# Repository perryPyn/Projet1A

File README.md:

Ce projet, réalisé dans le cadre du Semestre 6 à l'ENSEA (Année 2025-2026), consiste à développer un prototype de mesure de distance basé sur la technologie Time Of Flight (TOF). L'objectif est d'utiliser un capteur laser compact pour détecter des obstacles et commander une interface visuelle de retour.

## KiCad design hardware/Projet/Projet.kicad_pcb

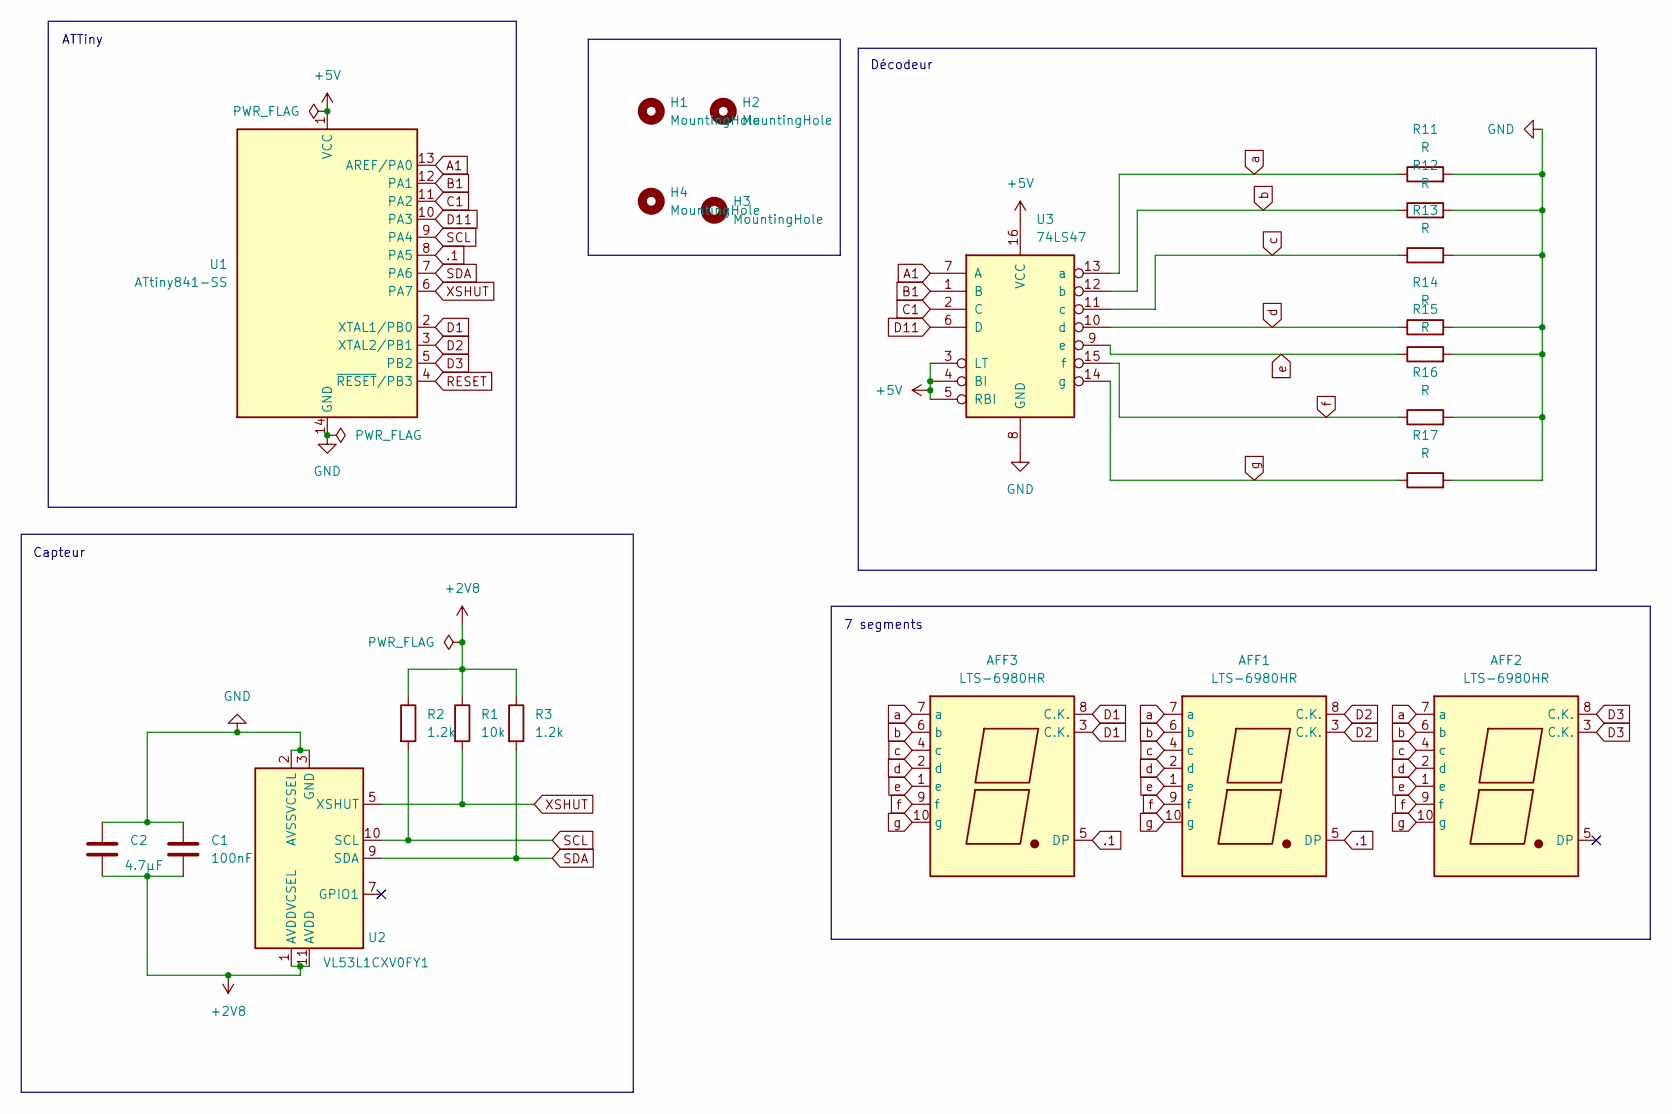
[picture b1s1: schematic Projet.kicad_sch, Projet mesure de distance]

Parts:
AFF1, AFF2, AFF3: LTS-6980HR; Sans titre_1
C1: 100nF; C_0603_1608Metric_Pad1.08x0.95mm_HandSolder
C2: 4.7µF; C_0603_1608Metric_Pad1.08x0.95mm_HandSolder
H1, H2, H3, H4: MountingHole; MountingHole_3.2mm_M3_DIN965_Pad
R1: 10k; R_0201_0603Metric_Pad0.64x0.40mm_HandSolder
R2, R3: 1.2k; R_0201_0603Metric_Pad0.64x0.40mm_HandSolder
R11, R12, R13, R14, R15, R16, R17: R; R_0201_0603Metric_Pad0.64x0.40mm_HandSolder
U1: ATtiny841-SS; SOIC-14_3.9x8.7mm_P1.27mm
U2: VL53L1CXV0FY1; ST_VL53L1x
U3: 74LS47; DIP-16_W7.62mm_SMDSocket_SmallPads

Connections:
+2V8: C1.2, C2.2, R1.1, R2.1, R3.1, U2.1 (AVDDVCSEL), U2.11 (AVDD)
+5V: U1.1 (VCC), U3.3 (LT), U3.4 (BI), U3.5 (RBI), U3.16 (VCC)
.1: AFF1.5 (DP), AFF3.5 (DP), U1.8 (PA5)
A1: U1.13 (AREF/PA0), U3.7 (A)
B1: U1.12 (PA1), U3.1 (B)
C1: U1.11 (PA2), U3.2 (C)
D1: AFF3.3 (C.K.), AFF3.8 (C.K.), U1.2 (XTAL1/PB0)
D2: AFF1.3 (C.K.), AFF1.8 (C.K.), U1.3 (XTAL2/PB1)
D3: AFF2.3 (C.K.), AFF2.8 (C.K.), U1.5 (PB2)
D11: U1.10 (PA3), U3.6 (D)
GND: C1.1, C2.1, R11.2, R12.2, R13.2, R14.2, R15.2, R16.2, R17.2, U1.14 (GND), U2.2 (AVSSVCSEL), U2.3 (GND), U2.4 (GND), U2.6 (GND), U2.12 (GND), U3.8 (GND)
RESET: U1.4 (~RESET/PB3)
SCL: R2.2, U1.9 (PA4), U2.10 (SCL)
SDA: R3.2, U1.7 (PA6), U2.9 (SDA)
XSHUT: R1.2, U1.6 (PA7), U2.5 (XSHUT)
a: AFF1.7 (a), AFF2.7 (a), AFF3.7 (a), R11.1, U3.13 (a)
b: AFF1.6 (b), AFF2.6 (b), AFF3.6 (b), R12.1, U3.12 (b)
c: AFF1.4 (c), AFF2.4 (c), AFF3.4 (c), R13.1, U3.11 (c)
d: AFF1.2 (d), AFF2.2 (d), AFF3.2 (d), R14.1, U3.10 (d)
e: AFF1.1 (e), AFF2.1 (e), AFF3.1 (e), R15.1, U3.9 (e)
f: AFF1.9 (f), AFF2.9 (f), AFF3.9 (f), R16.1, U3.15 (f)
g: AFF1.10 (g), AFF2.10 (g), AFF3.10 (g), R17.1, U3.14 (g)

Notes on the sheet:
Capteur
ATTiny
7 segments
Décodeur

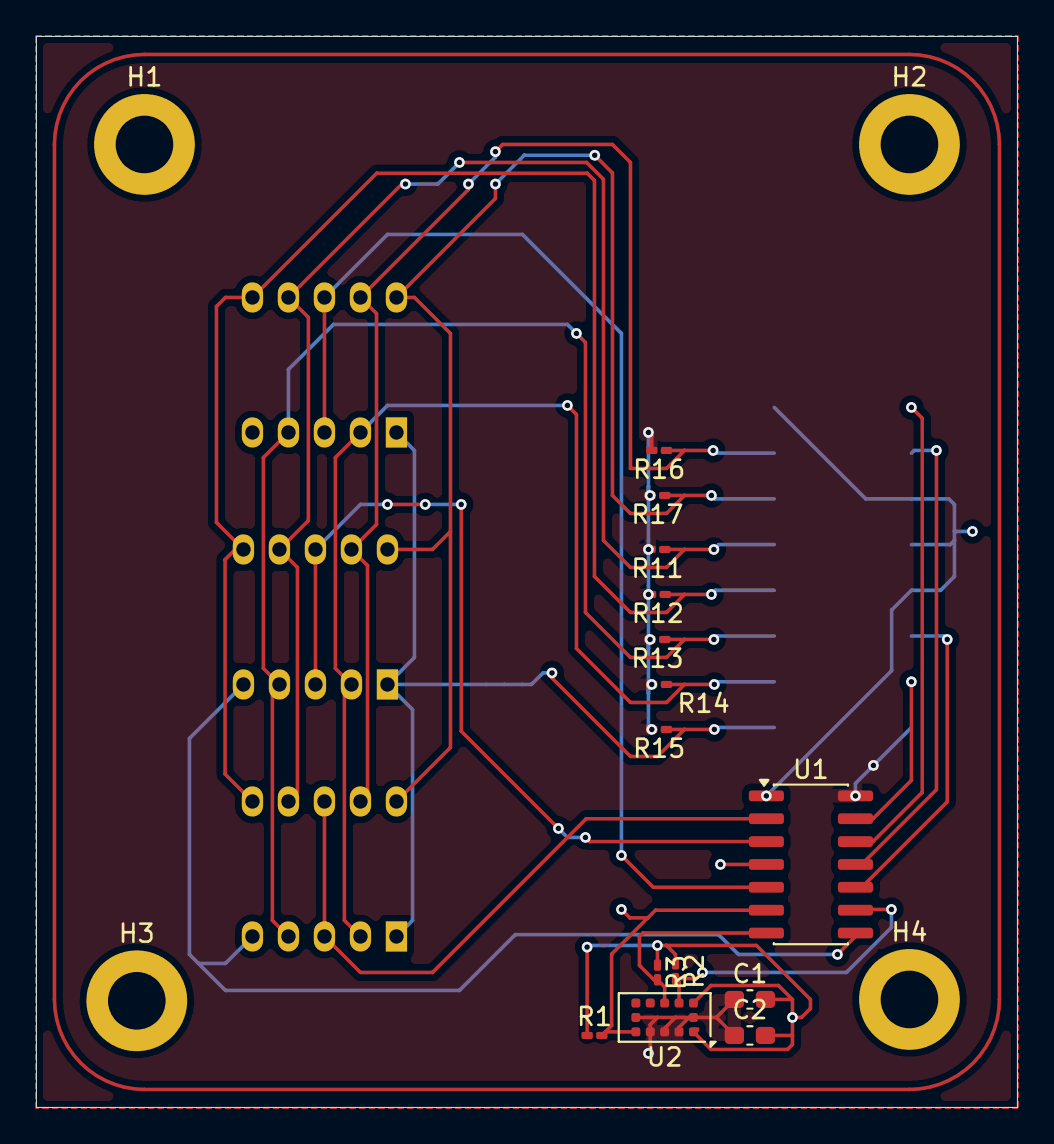
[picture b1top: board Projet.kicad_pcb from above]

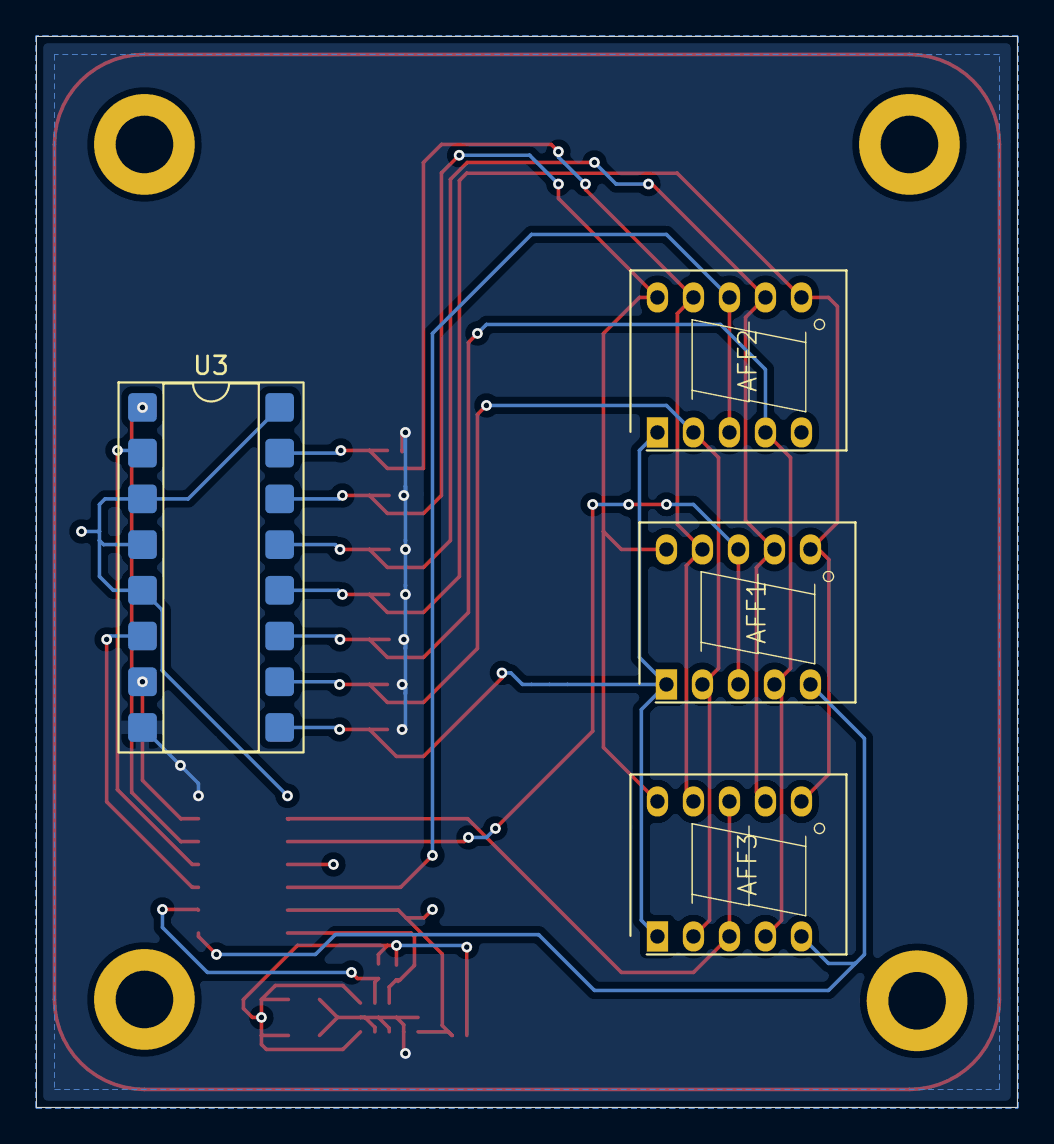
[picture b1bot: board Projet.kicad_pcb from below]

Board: 2 copper layers, 54.5 x 59.5 mm, 22 parts (4 on the bottom side), 21 nets.

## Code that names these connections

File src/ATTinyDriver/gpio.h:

#ifndef GPIO_H
#define GPIO_H

#include <avr/io.h>
#include <avr/interrupt.h>
#include "display.h"

/*
Schéma de configuration des pins de l'ATTiny841 :

                           ATTiny841
                        +------U------+
                  VCC  1|             |14  GND
     (DISPLAY_1)  PB0  2|             |13  PA0  (BIT_0)
     (DISPLAY_2)  PB1  3|             |12  PA1  (BIT_1)
         (RESET)  PB3  4|             |11  PA2  (BIT_2)
     (DISPLAY_3)  PB2  5|             |10  PA3  (BIT_3)
              ()  PA7  6|             |9   PA4  (I2C_SCL)
       (I2C_SDA)  PA6  7|             |8   PA5  (DECIMAL)
                        +-------------+

*/

/* --- Pins liason I2C --- */
#define I2C_SCL PA4 // Clock
#define I2C_SDA PA6 // Data

/* --- Pins pour I/O les display 7-segments --- */
#define DISPLAY_1 PB0
#define DISPLAY_2 PB1
#define DISPLAY_3 PB2

/* --- Pins pour le décodeur --- */
#define BIT_0 PA0
#define BIT_1 PA1
#define BIT_2 PA2
#define BIT_3 PA3

/* --- Pins pour les décimales des afficheurs --- */
#define DIXIEME  PA5
#define CENTIEME PA7



/* === Prototypage des fonctions === */
#ifdef __cplusplus
extern "C" {
#endif

extern volatile uint16_t numberToDisplay;
extern volatile uint8_t decimalPoint;
extern volatile uint8_t digit_1;
extern volatile uint8_t digit_2;
extern volatile uint8_t digit_3;

void PIN_Configure(void);
void PIN_Driver(volatile uint8_t *port, uint8_t pin, uint8_t state);

void Timer_Configure(void);

void setNumberToDisplay(uint16_t n);

#ifdef __cplusplus
}
#endif

#endif

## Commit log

2026-04-03 Initial commit: Ouverture du git
2026-04-03 schema elec updated
2026-04-03 maj driver attiny
2026-04-03 ajout pdf schema elec
2026-04-09 modifications driver, affiche le num du display
2026-04-09 modification de FormatNumber, fonctionne ok
2026-04-09 l'afficheur fonctionnent totalement, numberToDisplay sera la variable a modifier par la lecture du capteur
2026-04-09 implementation code capteur avec setter pour numberToDisplay. err 02 en sortie
2026-04-09 plus d'erreur 02, le capteur est trouvé
2026-04-09 deplacement de FormatNumber() dans le loop pour ne pas gener l'affichage
2026-04-13 code corrigé capteur
2026-04-13 ajout header code erreur et enlevé nesting
2026-04-13 ajout reset liason I2C en cas de crash
2026-04-13 ajout du watchdog
2026-04-13 réglages finaux capteur, grosse conso mais ok pour présentation
2026-04-13 init depuis la branch capteur
2026-04-13 fin sceance
2026-04-15 code pour enlever les 0 inutiles ok, manque le dp
2026-04-16 affichage dp fini
2026-04-16 import header opti
2026-04-16 update gitignore
2026-06-10 commit before resetting
